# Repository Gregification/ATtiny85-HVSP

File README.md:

### ATtiny85 HVSP for reset-locked device recovery (hand solderable)

> this hardware can be used on some chips of the same family after slight modification.

uses one ATTiny85 to recover other reset-locked ATtiny85's. Done by bringing the target ATtiny85 into HVSP mode, to reprogram the high fuse bits to `0xDF`.

[schematic view pdf](./demo/top%20level.pdf)

### Details
- Kicad 8.0
- master ATTiny85 operates at 8MHz(optional) with reset pin set to act as GPIO(required).
- made from common components. notable exceptions listed.
    - the [MIC2290](https://ww1.microchip.com/downloads/en/DeviceDoc/MIC2290.pdf) (boost converter IC to supply 12V; ~$1.00 for a order of 1 from Digikey), **this can be substituted** with a 12V supply tapped to the same trace.
    - the USB connector **can be substituted** with a 5V supply tapped to the same trace.

---

| Count | Component |
|-|-|
| 1 | MIC2290 boost converter IC |
| 1 | USB A plug |
| 1 | single pole switch (optional) |
| 1 | ATtiny85 |
| 1 | 44.2k Ohm |
| 5 | 5k Ohm |
| 4 | 1.2k ohm
| 1 | 10uH |
| 1 | 100nF |
| 2 | 10uF |
| 1 | diode (optional) |
| 2 | NPN BJT |
| 2 | PNP BJT |

---

<div style="display:flex; align-items:top;">

</div>

<p style="text-indent:1rem;">As shown, empty DIP socket holds target; master has a "dont remove" sticker. 100nF disk has been subsuited with a same sized SMD. 20k ohm pull down added on the buttons low side because the exact button used acts as a ~2M ohm resistor in its off state. Extra solder points because my maufacturing does not support plated vias, manually 'plating' was needed.</p>

---
<div style="display:flex; align-items:top;">
    
    <div style="margin-left:.5rem;" width="49%">
        <h3>Coloring</h3>
        <ul>
            <li>Green: reset-locked chip goes here</li>
            <li>White: go button</li>
            <li>Blue: master chip goes here</li>
            <li>red: 12V control circuitry</li>
            <li>yellow: 5V control circuitry</li>
        </ul>
        <h3>Setup</h3>
        <ol>
            <li>fab & assemble board</li>
            <li>program a master ATtiny85 using the code from the 'code' sub folder of this project. note that master ATtiny85 uses its reset pin as GPIO so the approate fuse bit needs set.</li>
            <li>put master in the blue outlined socket; notch to the left.</li>
        </ol>
        <h3>Operation</h3>
        <ol>
            <li>put reset-locked ATtiny85 in the green indicated socket; notch to the left.</li>
            <li>press & hold button for ~0.5 seconds</li>
            <li>target chip is now unbricked!</li>
        </ol>
    </div>
</div>

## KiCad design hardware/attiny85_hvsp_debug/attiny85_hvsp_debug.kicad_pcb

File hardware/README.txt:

sources & breif instructions for everything in the libraries folder
	clone the github / gitlab ones

https://github.com/Digi-Key/digikey-kicad-library
https://gitlab.com/kicad/libraries/kicad-symbols
https://gitlab.com/kicad/libraries/kicad-footprints

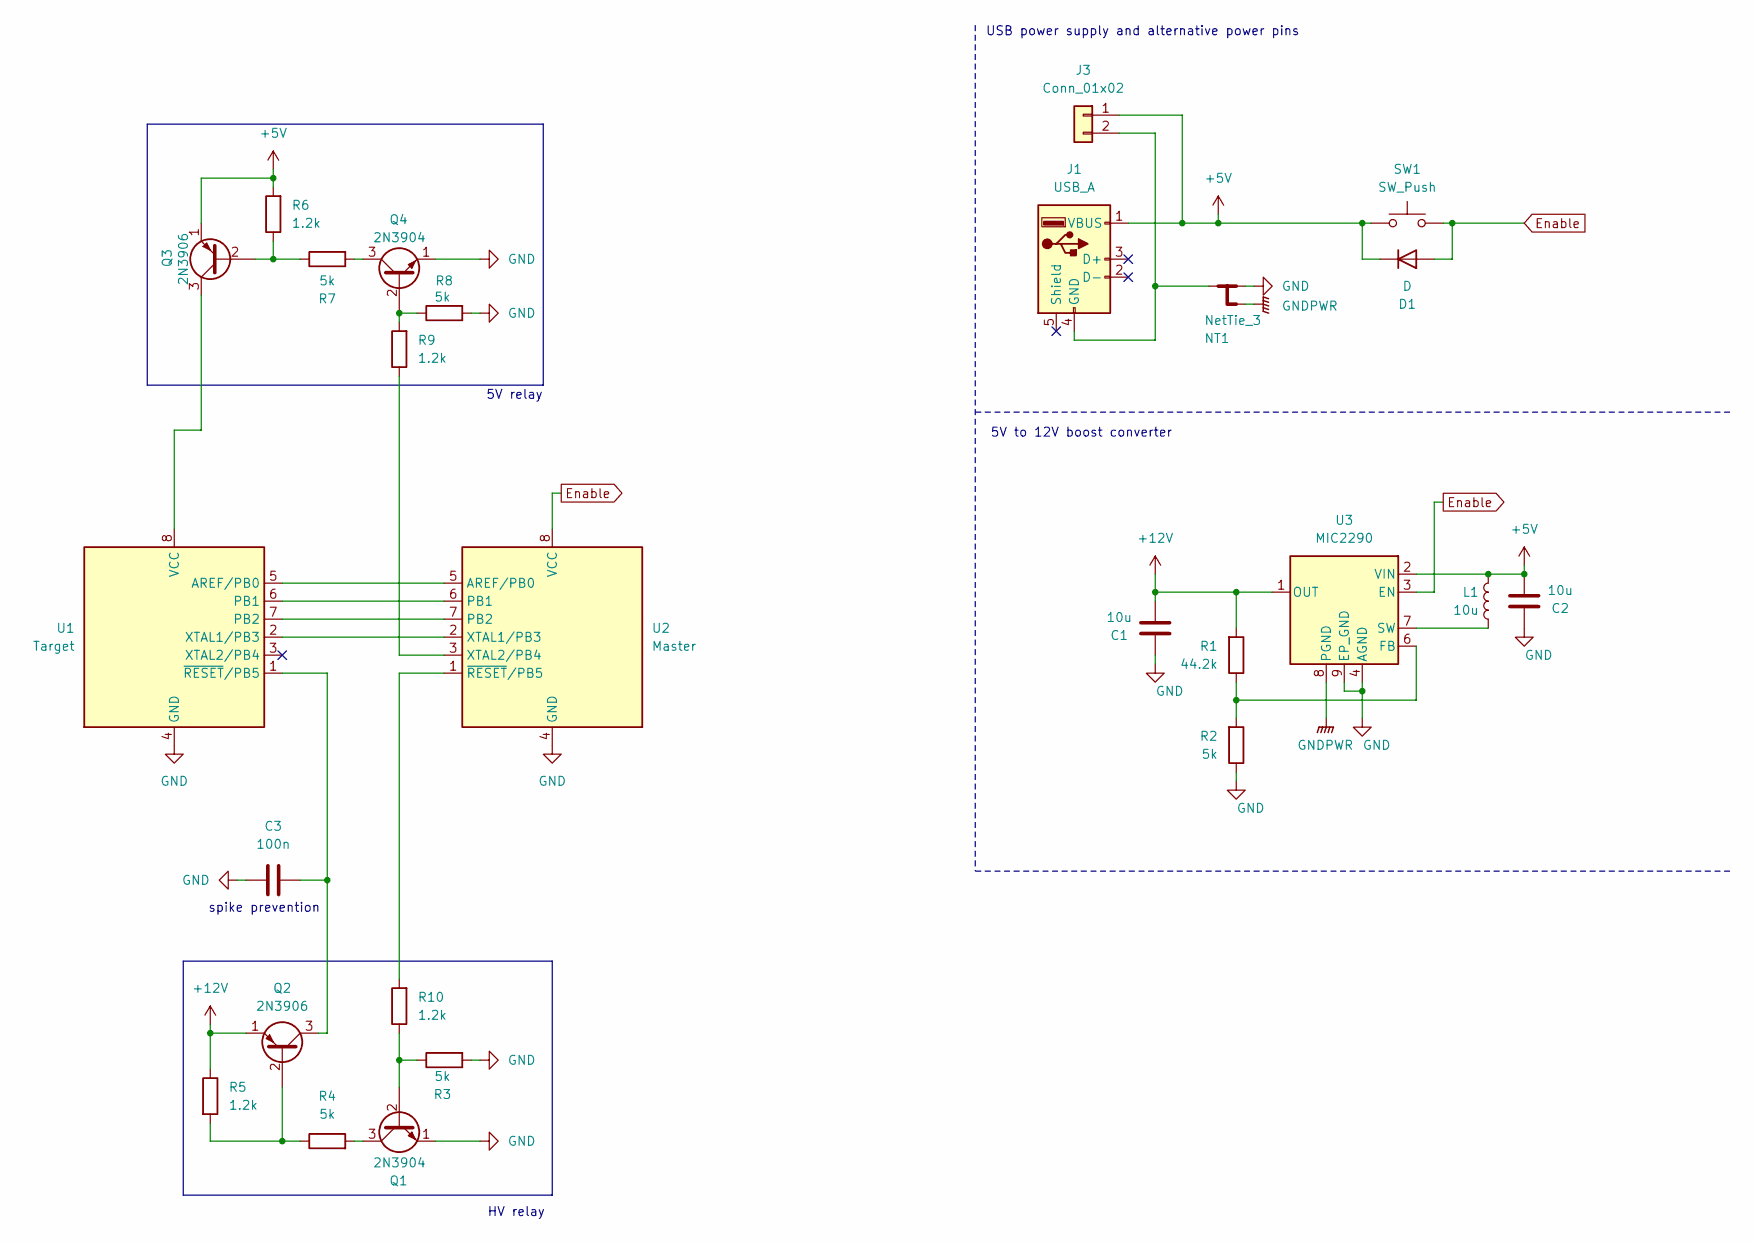
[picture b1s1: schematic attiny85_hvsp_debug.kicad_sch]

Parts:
C1, C2: 10u; C_1210_3225Metric
C3: 100n; C_Disc_D16.0mm_W5.0mm_P10.00mm
D1: D; D_5W_P10.16mm_Horizontal
J1: USB_A; USB_A_Molex_48037-2200_Horizontal
J3: Conn_01x02; PinHeader_1x02_P2.54mm_Vertical
L1: 10u; IDCP2218-01
NT1: NetTie_3; NetTie-3_SMD_Pad0.5mm
Q1, Q4: 2N3904; TO-92L_Wide
Q2, Q3: 2N3906; TO-92L_Wide
R1: 44.2k; R_1206_3216Metric
R2, R3, R4, R7, R8: 5k; R_Axial_DIN0207_L6.3mm_D2.5mm_P10.16mm_Horizontal
R5, R6, R9, R10: 1.2k; R_Axial_DIN0207_L6.3mm_D2.5mm_P10.16mm_Horizontal
SW1: SW_Push; SW_SPST_Omron_B3FS-101xP
U1: Target; DIP-8_W7.62mm
U2: Master; DIP-8_W7.62mm
U3: MIC2290; Micrel_MLF-8-1EP_2x2mm_P0.5mm_EP0.6x1.2mm

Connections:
+5V: C2.1, D1.1 (K), J1.1 (VBUS), J3.1, L1.1, Q3.1 (E), R6.2, SW1.1, U3.2 (VIN)
+12V: C1.1, Q2.1 (E), R1.2, R5.1, U3.1 (OUT)
Enable: D1.2 (A), SW1.2, U2.8 (VCC), U3.3 (EN)
GND: C1.2, C2.2, C3.1, NT1.1, Q1.1 (E), Q4.1 (E), R2.1, R3.2, R8.2, U1.4 (GND), U2.4 (GND), U3.4 (AGND), U3.9 (EP_GND)
GNDPWR: NT1.3, U3.8 (PGND)
unnamed: J1.4 (GND), J3.2, NT1.2
unnamed: Q1.2 (B), R3.1, R10.1
unnamed: Q1.3 (C), R4.2
unnamed: Q2.2 (B), R4.1, R5.2
unnamed: C3.2, Q2.3 (C), U1.1 (~RESET/PB5)
unnamed: Q3.2 (B), R6.1, R7.1
unnamed: Q3.3 (C), U1.8 (VCC)
unnamed: Q4.2 (B), R8.1, R9.2
unnamed: Q4.3 (C), R7.2
unnamed: U1.5 (AREF/PB0), U2.5 (AREF/PB0)
unnamed: U1.6 (PB1), U2.6 (PB1)
unnamed: U1.7 (PB2), U2.7 (PB2)
unnamed: U1.2 (XTAL1/PB3), U2.2 (XTAL1/PB3)
unnamed: R9.1, U2.3 (XTAL2/PB4)
unnamed: R10.2, U2.1 (~RESET/PB5)
unnamed: R1.1, R2.2, U3.6 (FB)
unnamed: L1.2, U3.7 (SW)

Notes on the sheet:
5V relay
HV relay
spike prevention
USB power supply and alternative power pins
5V to 12V boost converter

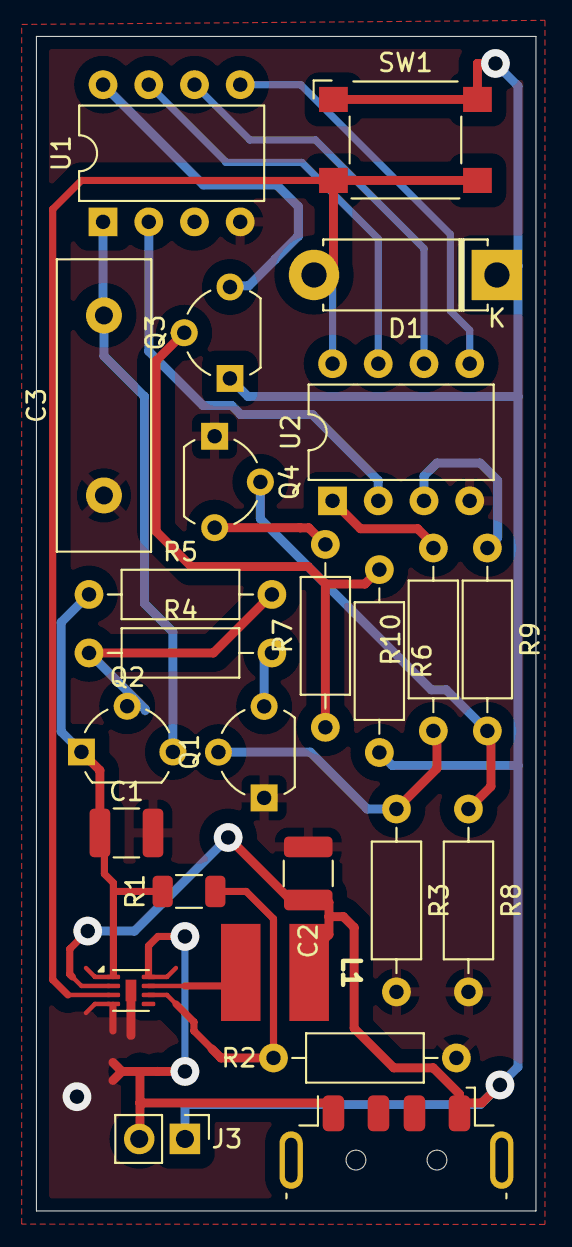
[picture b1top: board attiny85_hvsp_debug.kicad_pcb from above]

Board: 2 copper layers, 27.8 x 65.2 mm, 26 parts (0 on the bottom side), 22 nets.

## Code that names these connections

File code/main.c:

/**
 * ATtiny85 HVSP reset lock recovery
 *  code for master ATtiny85
 * 
 *  WARNING: ONLY TO BE USED AGAINST OTHER ATtiny85's
 * 
 * writes the fueses
 *  H   0xDF
 * 
 * note:
 *  - code is pov of the master, but datasheet is slave pov
 *  - master runs at 8 MHz
 *  - master has Reset pin as GPIO
 */

#ifndef __AVR_ATtiny85__
#define __AVR_ATtiny85__
#endif

#ifndef F_CPU
#define F_CPU 8000000UL
#endif

#define CLK_DELAY_us    3   

#include <stdbool.h>
#include <stdint.h>
#include <avr/io.h>
#include <util/delay.h>

// uP chapter 20.6
#define SDI             _BV(PB0)
#define SII             _BV(PB1)
#define SDO             _BV(PB2)
#define SCI             _BV(PB3)
#define VCC_CTRL        _BV(PB4)
#define HV_CTRL         _BV(PB5)
#define PROG_ENABLE0    SDI
#define PROG_ENABLE1    SII
#define PROG_ENABLE2    SDO

typedef struct {
    uint8_t input;
    uint8_t instruction;
    uint8_t output;
} Instr;
void transfer_instruction(Instr* txrx, uint8_t len);

int main(){
    //------------------------------------------------------------------------------------
    //  WARNING: ONLY TO BE USED AGAINST OTHER ATtiny85's
    //------------------------------------------------------------------------------------
    
    //------------------------------------------------------------------------------------
    //  init
    //------------------------------------------------------------------------------------

    DDRB |= SCI | SII | SDI | SDO | HV_CTRL | VCC_CTRL; // outputs

    // everything to low
    PORTB &= ~(SCI | SII | SDI | SDO | HV_CTRL | VCC_CTRL);

    //------------------------------------------------------------------------------------
    // enter HVSP mode - uP chapter 20.7.1
    //------------------------------------------------------------------------------------

    // 1. Set Prog_enable pins listed in Table 20-14 to “000”, RESET pin and VCC to 0V.
    PORTB &= ~(PROG_ENABLE0 | PROG_ENABLE1 | PROG_ENABLE2 | HV_CTRL | VCC_CTRL);

    _delay_ms(100); // wait for latches

    // 2. Apply 4.5 - 5.5V between VCC and GND. Ensure that VCC reaches at least 1.8V within the next 20 μs.
    PORTB |= VCC_CTRL;

    // 3. Wait 20 - 60 μs, and apply 11.5 - 12.5V to RESET.
    _delay_us(30);
    PORTB |= HV_CTRL;

    // 4. Keep the Prog_enable pins unchanged for at least 10 μs after the High-voltage has been applied to
    //      ensure the Prog_enable Signature has been latched.
    _delay_us(15);

    // 5. Release the Prog_enable[2] pin to avoid drive contention on the Prog_enable[2]/SDO pin.
    
    // set PROG_ENABLE2 to Hi-Z input
    DDRB    &= ~PROG_ENABLE2;         // set as input
    PORTB   &= ~PROG_ENABLE2;         // disable bias resistors

    // 6. Wait at least 300 μs before giving any serial instructions on SDI/SII.
    _delay_us(350);


    //------------------------------------------------------------------------------------
    // program high fuses
    //------------------------------------------------------------------------------------
    {
        Instr *instrs;
        
        // set fuse bits to 0xDF
        instrs = (Instr[4]){
                  {0x40  ,   0x4C},
                  {0xDF  ,   0x2C},
                  {0x00  ,   0x74},
                  {0x00  ,   0x7C},
                };
        transfer_instruction(instrs, 4);
    }

    //------------------------------------------------------------------------------------
    // exit
    //------------------------------------------------------------------------------------
    
    PORTB &= ~(VCC_CTRL | HV_CTRL);

    while(true)
        ;

    return 0;
}

void transfer_instruction(Instr* txrx, uint8_t len){
    if(!txrx)
        return;

    /* basically just 11 bit SPI with the following gimics
     *  - 2 parallel data lines, SDI and SII
     *  - SDI, SII, and SDO are 8 bit values, MSB first, left aligned within the 11 bits
     *  - SDI and SII uses SPI mode 1
     *  - SDO uses SPI mode 0
     *  - 0's are used as padding bits
     */

    PORTB &= ~SCI; // ensure clock is low (it should already be low)

    uint8_t packet_i;
    for(packet_i = 0; packet_i < len; packet_i++){
        
        // this delay is not necesasry but makes waveform easier to read
        _delay_us(CLK_DELAY_us);

        uint8_t bit_i;
        for(bit_i = 0; bit_i < 11; bit_i++){

            _delay_us(CLK_DELAY_us);
            PORTB |= SCI;

            _delay_us(CLK_DELAY_us);
            PORTB &= ~SCI;

            // SDO
            txrx[packet_i].output |= ((PINB | SDO) != 0) << (7-bit_i);

            // SDI
            if((txrx[packet_i].input       >> (7-bit_i)) & 1)
                PORTB |= SDI;
            else
                PORTB &= ~SDI;

            // SII
            if((txrx[packet_i].instruction >> (7-bit_i)) & 1)
                PORTB |= SII;
            else
                PORTB &= ~SII;

        }
    }
}

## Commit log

2024-12-04 brought over from homelab repo
2024-12-16 brute forced BJT design
2024-12-16 womp owpm
2024-12-18 updated readme & tidied up project
2024-12-18 readme looks funky
